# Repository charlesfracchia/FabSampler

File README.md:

FabSampler
==========

A board able to collect data from the fab sensor boards (eg: FabECG) and relay the data over serial
by Charles Fracchia and Adam Marblestone
Copyright 2012

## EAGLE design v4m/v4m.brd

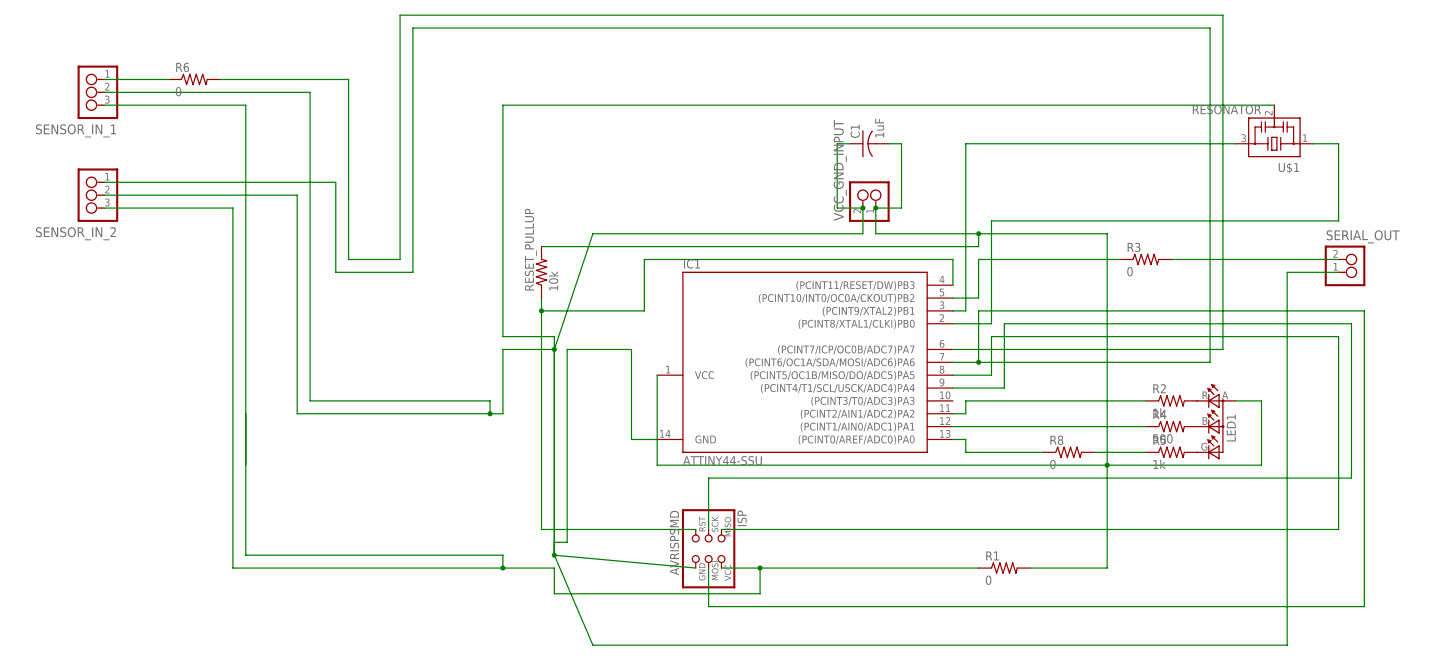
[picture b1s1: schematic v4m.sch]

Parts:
C1: 1uF; C1206
IC1: ATTINY44-SSU; SOIC14
ISP: AVRISPSMD; 2X03SMD
LED1: LEDRGBOLD; P-LCC-4-3
R1, R3, R6, R8: 0; R1206
R2, R5: 1k; R1206
R4: 500; R1206
RESET_PULLUP: 10k; R1206
SENSOR_IN_1, SENSOR_IN_2: 3_PIN_HEADERHEADER; SMT_PINS_3
SERIAL_OUT: 2_PIN_HEADERHEADER; SMT_PINS_2
U$1: RESONATOR; EFOBM
VCC_GND_INPUT: 2_PIN_HEADERHEADER; SMT_PINS_2

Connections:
ATTINY45: IC1.9 ((PCINT4/T1/SCL/USCK/ADC4)PA4), ISP.3 (SCK)
unnamed: C1.2, IC1.1 (VCC), LED1.A (A2), R1.2, RESET_PULLUP.2, VCC_GND_INPUT.1
unnamed: R5.1, R8.2
unnamed: IC1.8 ((PCINT5/OC1B/MISO/DO/ADC5)PA5), ISP.1 (MISO)
unnamed: IC1.4 ((PCINT11/RESET/DW)PB3), ISP.5 (RST), RESET_PULLUP.1
unnamed: IC1.5 ((PCINT10/INT0/OC0A/CKOUT)PB2), R3.1
unnamed: IC1.2 ((PCINT8/XTAL1/CLKI)PB0), U$1.1
unnamed: ISP.2 (VCC), R1.1, SENSOR_IN_1.3, SENSOR_IN_2.3
unnamed: R6.1, SENSOR_IN_1.1
unnamed: LED1.R (CRED), R2.2
unnamed: LED1.B (CBLUE), R4.2
unnamed: IC1.6 ((PCINT7/ICP/OC0B/ADC7)PA7), R6.2
unnamed: IC1.3 ((PCINT9/XTAL2)PB1), U$1.3
unnamed: LED1.G (CGREEN), R5.2
unnamed: IC1.13 ((PCINT0/AREF/ADC0)PA0), R8.1
unnamed: C1.1, IC1.14 (GND), ISP.6 (GND), SENSOR_IN_1.2, SENSOR_IN_2.2, SERIAL_OUT.1, U$1.2, VCC_GND_INPUT.2
unnamed: IC1.11 ((PCINT2/AIN1/ADC2)PA2), R2.1
unnamed: IC1.12 ((PCINT1/AIN0/ADC1)PA1), R4.1
unnamed: R3.2, SERIAL_OUT.2
unnamed: IC1.7 ((PCINT6/OC1A/SDA/MOSI/ADC6)PA6), ISP.4 (MOSI), SENSOR_IN_2.1

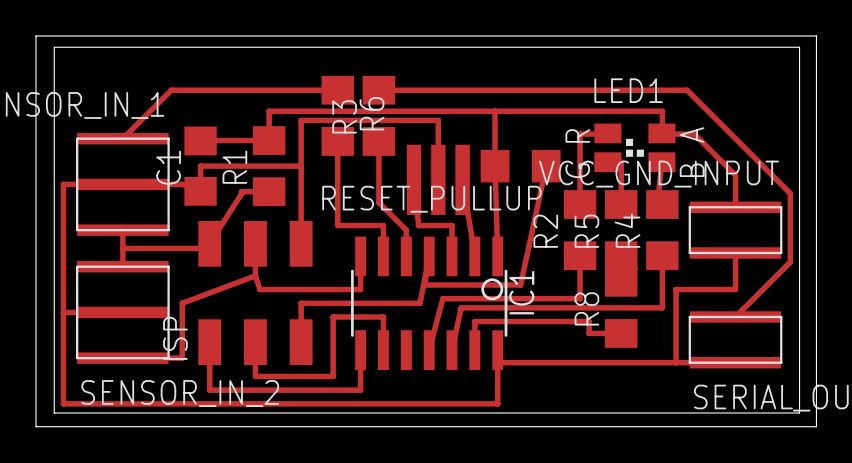
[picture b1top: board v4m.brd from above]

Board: 2 copper layers, 43.4 x 21.7 mm, 17 parts (0 on the bottom side), 20 nets.

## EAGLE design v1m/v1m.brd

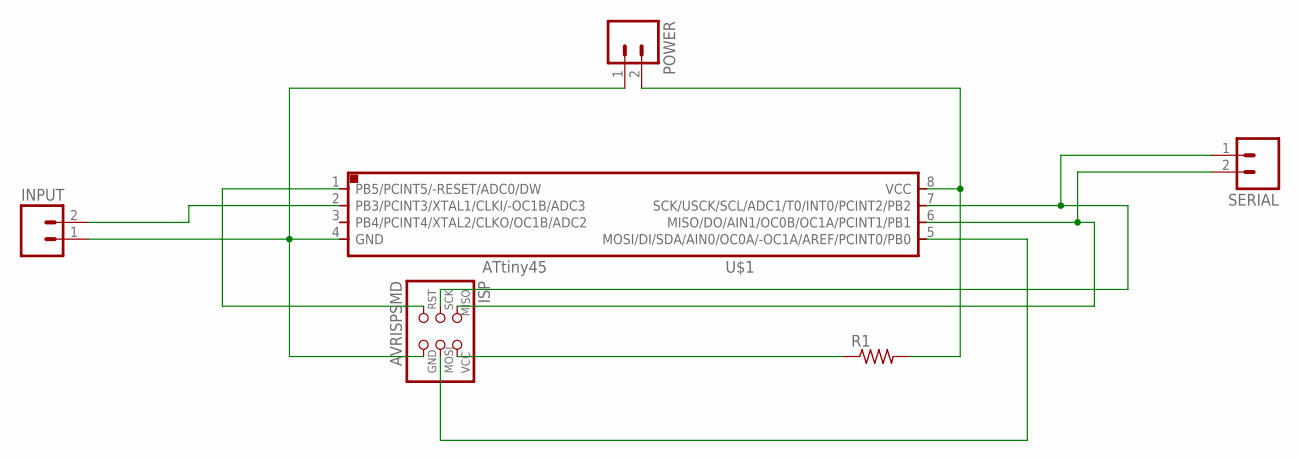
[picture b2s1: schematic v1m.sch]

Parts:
INPUT: M02JUST2PADS; JST-2-SMD-VERT
ISP: AVRISPSMD; 2X03SMD
POWER: M02JUST2PADS; JST-2-SMD-VERT
R1: RES-US1206; R1206
SERIAL: M02JUST2PADS; JST-2-SMD-VERT
U$1: ATTINY45SI; SOIC8

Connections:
ATTINY45: ISP.3 (SCK), SERIAL.1, U$1.7 (SCK/USCK/SCL/ADC1/T0/INT0/PCINT2/PB2)
unnamed: INPUT.1, ISP.6 (GND), POWER.1, U$1.4 (GND)
unnamed: POWER.2, R1.2, U$1.8 (VCC)
unnamed: ISP.4 (MOSI), U$1.5 (MOSI/DI/SDA/AIN0/OC0A/-OC1A/AREF/PCINT0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)
unnamed: ISP.1 (MISO), SERIAL.2, U$1.6 (MISO/DO/AIN1/OC0B/OC1A/PCINT1/PB1)
unnamed: ISP.5 (RST), U$1.1 (PB5/PCINT5/-RESET/ADC0/DW)
unnamed: INPUT.2, U$1.2 (PB3/PCINT3/XTAL1/CLKI/-OC1B/ADC3)
unnamed: ISP.2 (VCC), R1.1

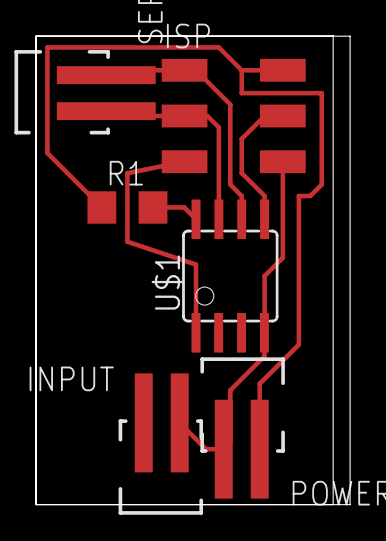
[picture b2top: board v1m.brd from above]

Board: 2 copper layers, 17.4 x 26.0 mm, 6 parts (0 on the bottom side), 8 nets.

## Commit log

2012-10-11 Added v1m and v2m
    v1m is grossly wrong, is missing a number of components for it to be
    even programmable.
    v2m is still in an unhappy state where based on the current design, the
    fuses get burnt on the chip once and then we're unable to do anything
    else.
2012-10-24 v3m, v4m and v5m added
    Added the versions and changed the gitignore to include temp board and
    schematic files
2012-10-24 Cleanup in folders
    Cleaned up the folders, the gitignore for temp files is not working as
    is...

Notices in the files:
parts and their libraries:
Charles-Connectors: Licensing: CC v3.0 Share-Alike You are welcome to use this library for commercial purposes.
